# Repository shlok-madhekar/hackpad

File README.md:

## Case Screenshot

## PCB Screenshot

## Schematic Screenshot

## Overall Screenshot

## BOM

- 6x Cherry MX Switches
- 2x SK6812 MINI Leds
- 1x XIAO RP2040
- 6x Blank DSA Keycaps

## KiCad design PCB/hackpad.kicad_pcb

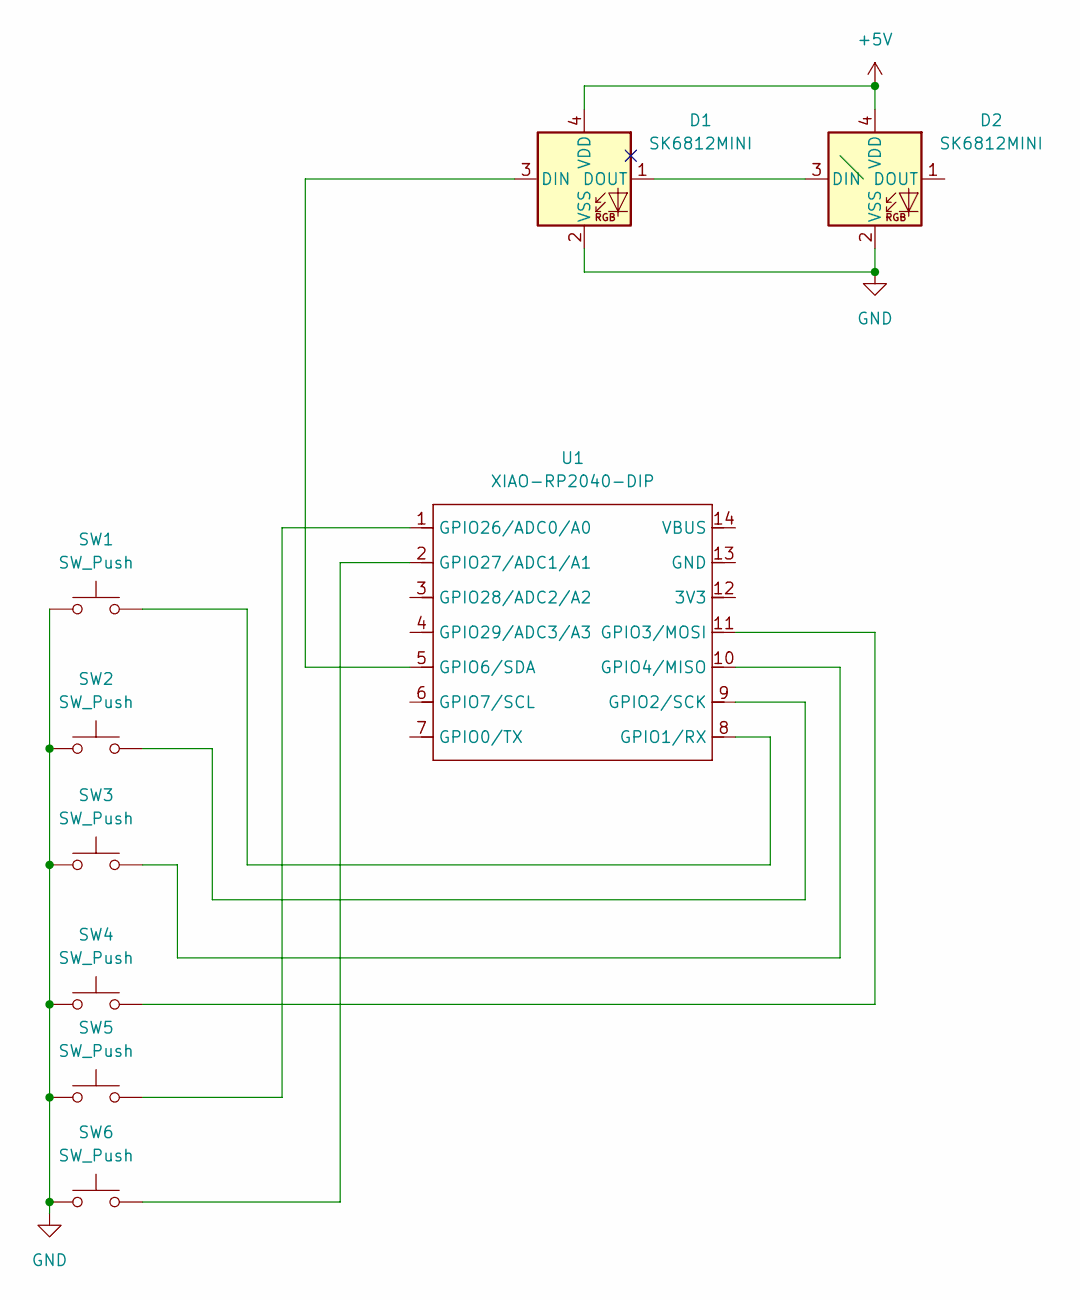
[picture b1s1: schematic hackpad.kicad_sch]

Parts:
D1, D2: SK6812MINI; LED_SK6812MINI_PLCC4_3.5x3.5mm_P1.75mm
SW1, SW2, SW3, SW4, SW5, SW6: SW_Push; SW_Cherry_MX_1.00u_PCB
U1: XIAO-RP2040-DIP

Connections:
+5V: D1.4 (VDD), D2.4 (VDD)
GND: D1.2 (VSS), D2.2 (VSS), SW1.1, SW2.1, SW3.1, SW4.1, SW5.1, SW6.1
unnamed: D1.3 (DIN), U1.5 (GPIO6/SDA)
unnamed: D1.1 (DOUT), D2.3 (DIN)
unnamed: SW1.2, U1.8 (GPIO1/RX)
unnamed: SW2.2, U1.9 (GPIO2/SCK)
unnamed: SW4.2, U1.11 (GPIO3/MOSI)
unnamed: SW3.2, U1.10 (GPIO4/MISO)
unnamed: SW5.2, U1.1 (GPIO26/ADC0/A0)
unnamed: SW6.2, U1.2 (GPIO27/ADC1/A1)

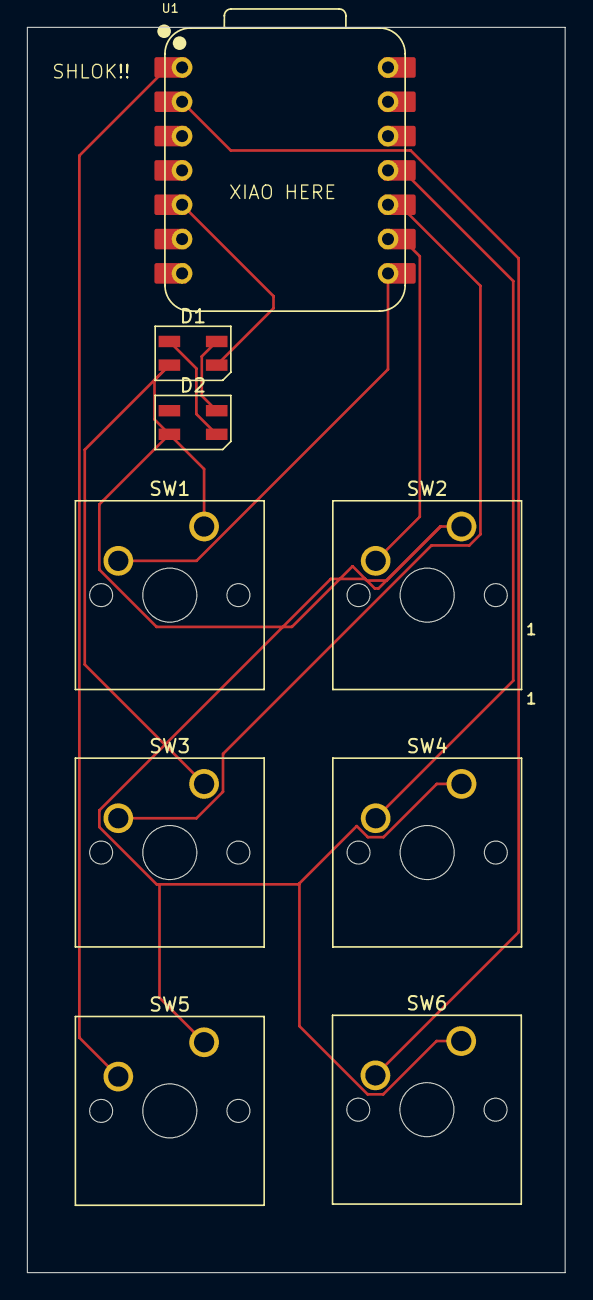
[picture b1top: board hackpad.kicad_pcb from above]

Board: 2 copper layers, 39.8 x 92.2 mm, 9 parts (0 on the bottom side), 10 nets.
